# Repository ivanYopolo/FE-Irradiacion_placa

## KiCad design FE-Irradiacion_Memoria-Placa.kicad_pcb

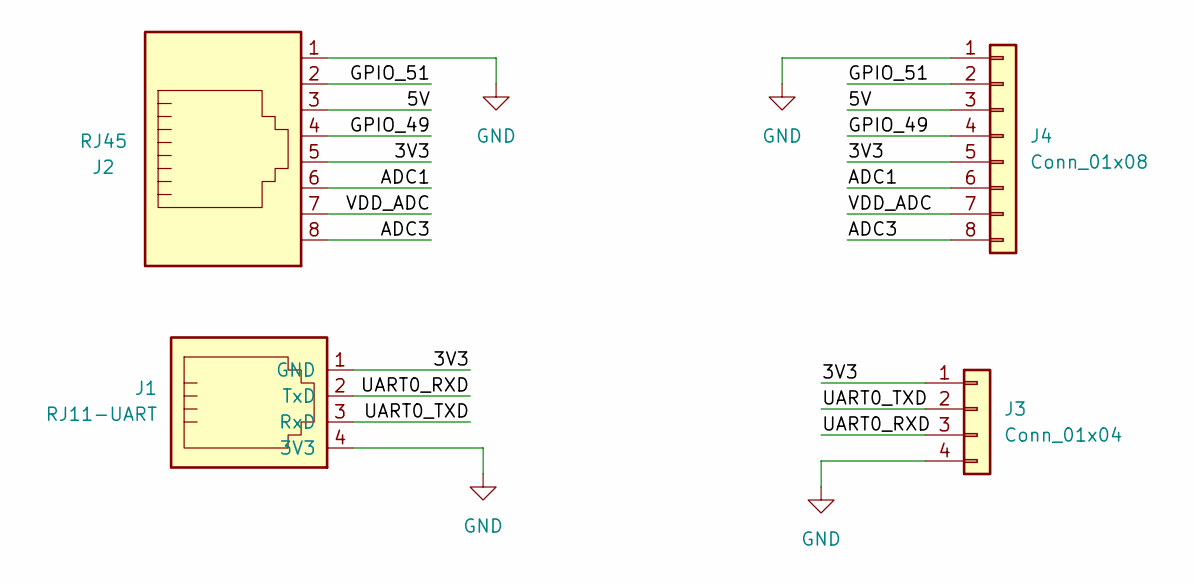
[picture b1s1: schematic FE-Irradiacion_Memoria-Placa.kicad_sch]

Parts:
J1: RJ11-UART; RJ11_LIFEDE
J2: RJ45; RJ45_Amphenol_RJHSE538X
J3: Conn_01x04; PinSocket_1x04_P2.54mm_Vertical
J4: Conn_01x08; PinSocket_1x08_P2.54mm_Vertical

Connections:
/3V3: J1.1 (GND), J2.5, J3.1, J4.5
/5V: J2.3, J4.3
/ADC1: J2.6, J4.6
/ADC3: J2.8, J4.8
/GPIO_49: J2.4, J4.4
/GPIO_51: J2.2, J4.2
/UART0_RXD: J1.2 (TxD), J3.3
/UART0_TXD: J1.3 (RxD), J3.2
/VDD_ADC: J2.7, J4.7
GND: J1.4 (3V3), J2.1, J3.4, J4.1

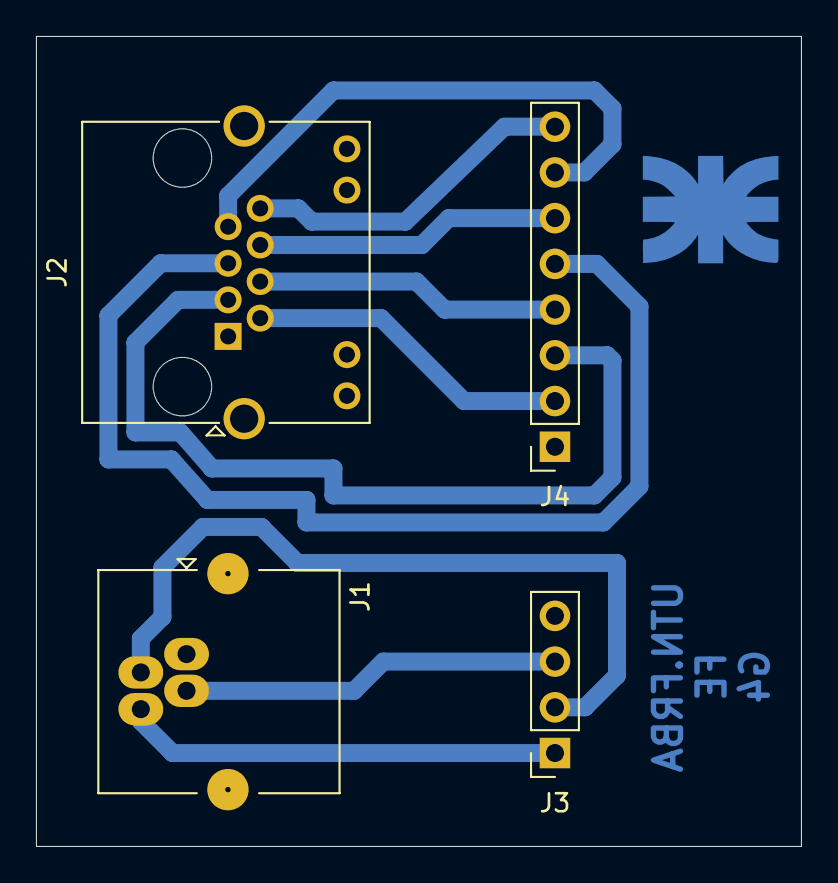
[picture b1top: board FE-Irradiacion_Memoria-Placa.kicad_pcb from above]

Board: 2 copper layers, 42.5 x 45.0 mm, 4 parts (0 on the bottom side), 10 nets.
